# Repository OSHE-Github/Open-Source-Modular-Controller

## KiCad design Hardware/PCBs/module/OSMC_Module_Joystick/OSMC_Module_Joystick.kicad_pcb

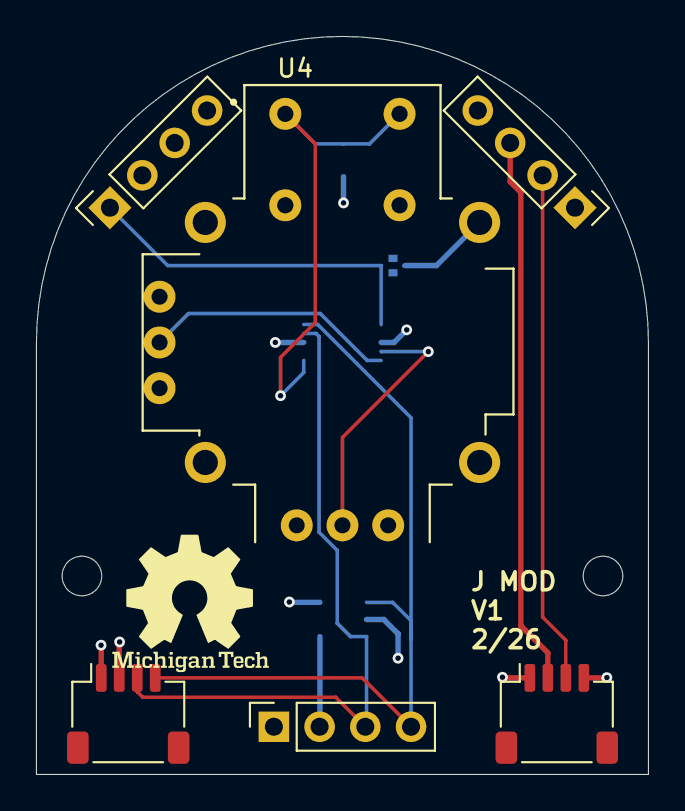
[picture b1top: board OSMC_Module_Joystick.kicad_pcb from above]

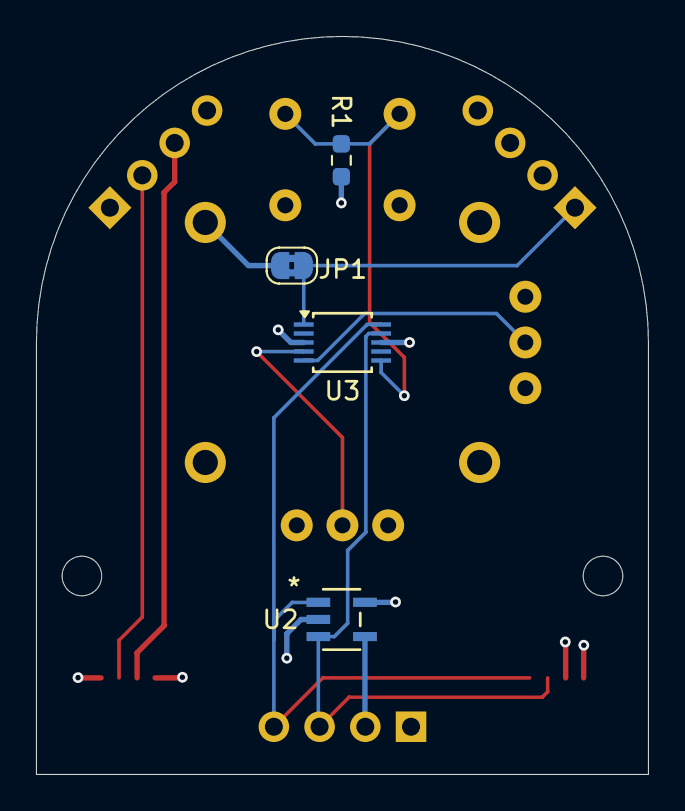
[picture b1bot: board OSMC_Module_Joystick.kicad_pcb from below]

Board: 4 copper layers, 34.0 x 41.0 mm, 6 parts (4 on the bottom side), 10 nets.

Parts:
JP1: SolderJumper_2_Bridged; SolderJumper-2_P1.3mm_Bridged2Bar_RoundedPad1.0x1.5mm
R1: 100K; R_0603_1608Metric_Pad0.98x0.95mm_HandSolder
U1: OSMC Module Board w/pins; Module standard pin large
U2: 24LC02BT-I/OT; SOT-23-5_MC_MCH
U3: ADS1115IDGS; TSSOP-10_3x3mm_P0.5mm
U4: COM-09032; XDCR_COM-09032

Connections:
/3v3: R1.2, U1.2 (Vdd), U1.6 (Vdd), U1.12 (Det), U1.13 (Int), U2.4 (VCC), U3.8 (VDD), U4.H1 (H+), U4.V1 (V+)
/5V: U1.10 (5V), U1.15 (5V)
/A1: JP1.2 (B), U1.20 (A1), U3.1 (ADDR)
/INT: U1.11 (OPT), U1.14 (OPT)
/SCL: U1.4 (SCL), U1.8 (SCL), U2.1 (SCL), U3.10 (SCL)
/SDA: U1.3 (SDA), U1.7 (SDA), U2.3 (SDA), U3.9 (SDA)
GND: JP1.1 (A), U1.1 (Gnd), U1.5 (Gnd), U1.9 (Gnd), U1.16 (GND), U2.2 (VSS), U2.5 (WP), U3.3 (GND), U4.B2A (SEL-), U4.B2B (SEL-), U4.H3 (H-), U4.S1 (SHIELD), U4.S2 (SHIELD__1), U4.S3 (SHIELD__2), U4.S4 (SHIELD__3), U4.V3 (V-)
unnamed: U3.4 (AIN0), U4.H2 (H)
unnamed: U3.5 (AIN1), U4.V2 (V)
unnamed: R1.1, U3.6 (AIN2), U4.B1A (SEL+), U4.B1B (SEL+)

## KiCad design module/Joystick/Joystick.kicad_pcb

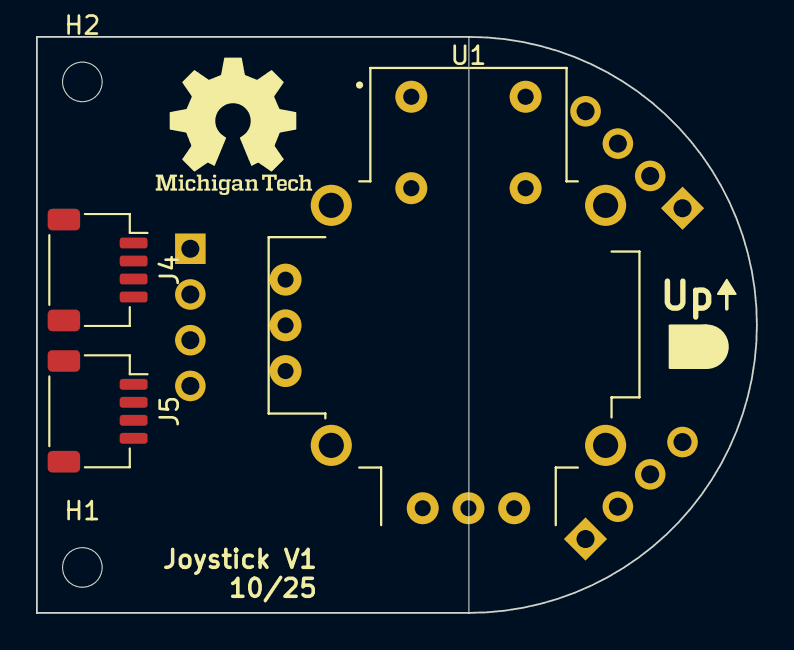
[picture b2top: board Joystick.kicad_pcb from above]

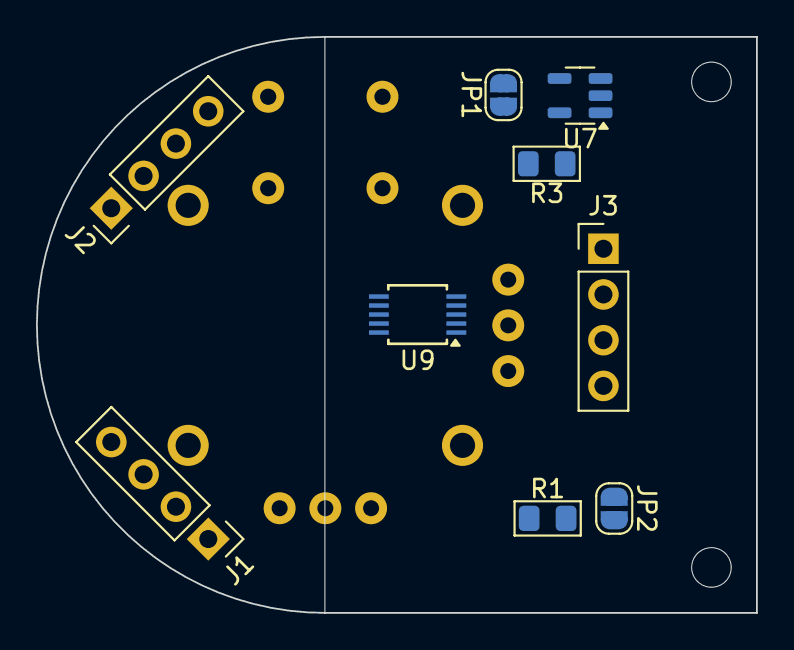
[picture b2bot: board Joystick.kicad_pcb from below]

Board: 2 copper layers, 40.0 x 32.0 mm, 14 parts (9 on the bottom side), 10 nets, no tracks yet.

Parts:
H1, H2: MountingHole; MountingHole_2.2mm_M2
J1: Right Arm; PinHeader_1x04_P2.54mm_Vertical
J2: Right Leg; PinHeader_1x04_P2.54mm_Vertical
J3: Header 1; PinHeader_1x04_P2.54mm_Vertical
J4: Left Arm; JST_SH_SM04B-SRSS-TB_1x04-1MP_P1.00mm_Horizontal
J5: Header 1; JST_SH_SM04B-SRSS-TB_1x04-1MP_P1.00mm_Horizontal
JP1: WP; SolderJumper-2_P1.3mm_Open_RoundedPad1.0x1.5mm
JP2: int; SolderJumper-2_P1.3mm_Open_RoundedPad1.0x1.5mm
R1, R3: 100k; R_0805_2012Metric_Pad1.15x1.40mm_HandSolder
U1: COM-09032; XDCR_COM-09032
U7: 24AA02-OT; SOT-23-5
U9: ADS1115IDGS; TSSOP-10_3x3mm_P0.5mm

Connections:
+5V: U1.H1 (H+), U1.V1 (V+)
/5V: J1.1, J5.1
/Gnd: J1.2, J3.4, J4.4, J5.2, R1.1, R3.1, U7.2 (V_{SS}), U9.1 (ADDR), U9.3 (GND)
/IO1: J2.4, J5.3
/SCL: J3.1, J4.1, U7.1 (SCL), U9.10 (SCL)
/SDA: J3.2, J4.2, U7.3 (SDA), U9.9 (SDA)
/Vdd: J3.3, J4.3, JP1.2 (B), JP2.2 (B), U7.4 (V_{CC}), U9.8 (VDD)
/int: J1.4, J5.4, JP2.1 (A), R1.2
/wp: JP1.1 (A), R3.2, U7.5 (WP)
GND: U1.B2A (SEL-), U1.H3 (H-), U1.S1 (SHIELD), U1.S2 (SHIELD__1), U1.S3 (SHIELD__2), U1.S4 (SHIELD__3), U1.V3 (V-)

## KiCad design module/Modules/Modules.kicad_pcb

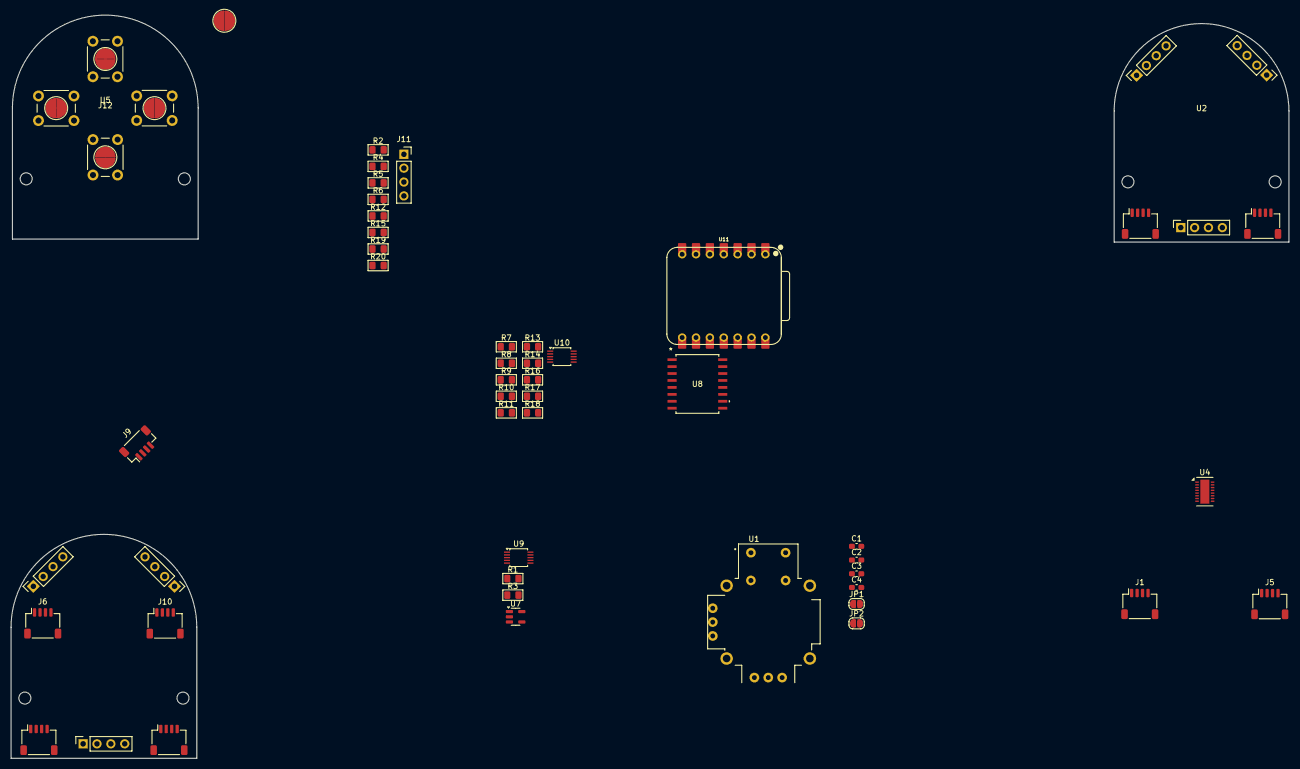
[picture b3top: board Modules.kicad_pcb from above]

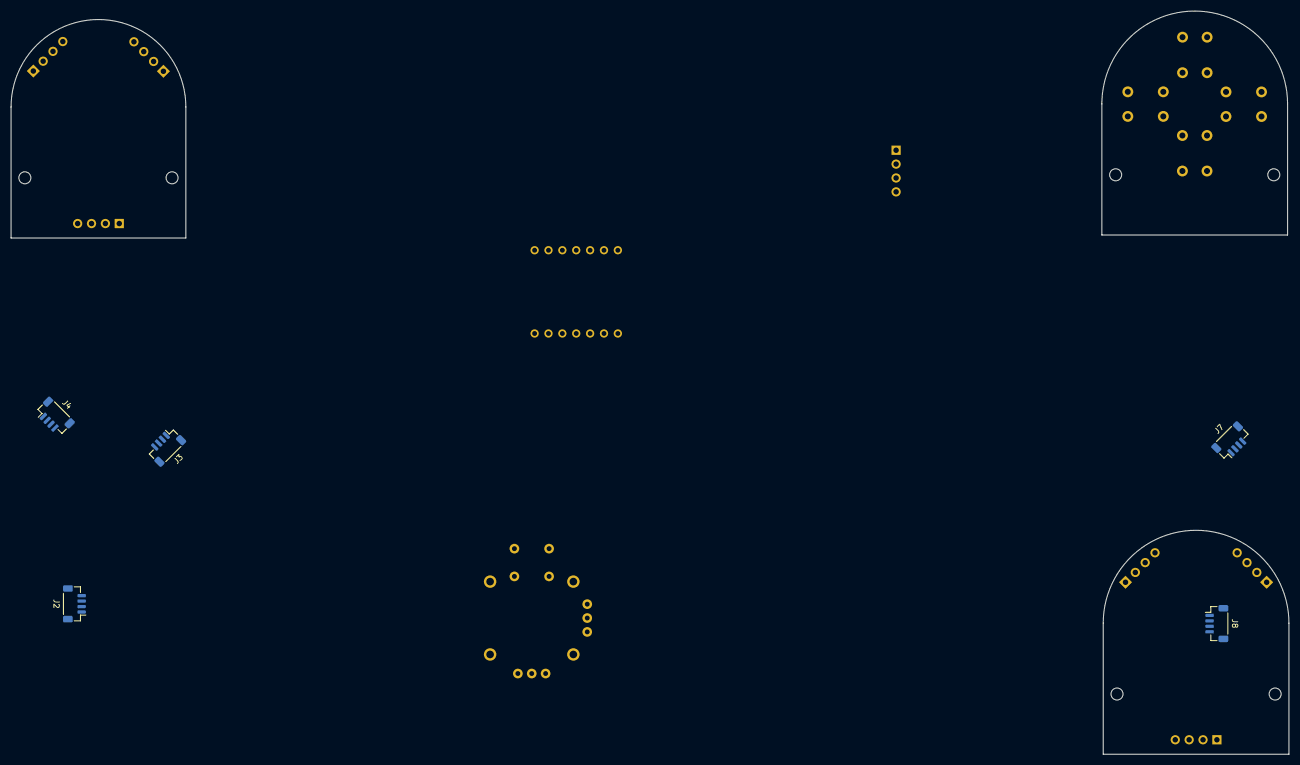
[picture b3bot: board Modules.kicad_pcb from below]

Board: 2 copper layers, 49 parts (5 on the bottom side), 32 nets, no tracks yet.

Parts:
C1, C2: .1 u; C_0603_1608Metric_Pad1.08x0.95mm_HandSolder
C3, C4: C; C_0603_1608Metric_Pad1.08x0.95mm_HandSolder
J1, J5, J6, J10: JST SH; JST_SH_SM04B-SRSS-TB_1x04-1MP_P1.00mm_Horizontal
J2, J3, J4, J7, J8, J9: Conn_01x04; JST_SH_BM04B-SRSS-TB_1x04-1MP_P1.00mm_Vertical
J11: JST SH; PinSocket_1x04_P2.54mm_Vertical
J12: Conn_01x08_Socket; Button Spacing
JP1: WP; SolderJumper-2_P1.3mm_Open_RoundedPad1.0x1.5mm
JP2: Det; SolderJumper-2_P1.3mm_Open_RoundedPad1.0x1.5mm
R1, R2, R3, R4, R5, R6: 100k; R_0805_2012Metric_Pad1.15x1.40mm_HandSolder
R7, R8, R9, R10, R11, R12, R13, R14, R15, R16, R17, R18, R19, R20: 10k; R_0805_2012Metric_Pad1.15x1.40mm_HandSolder
SW1: SW_Push; Membrane Button semi 4 mm
U1: COM-09032; XDCR_COM-09032
U2: OSMC Module Board w/pins; Module standard pin small
U4: OSMC Module Board; DFN-16-1EP_3x5mm_P0.5mm_EP1.66x4.4mm
U5: OSMC Module Board w/pins; Module standard large
U6: OSMC Module Board; Module standard pin large
U7: 24AA02-OT; SOT-23-5
U8: PCF8574DWR; DW16-L
U9: ADS1115IDGS; TSSOP-10_3x3mm_P0.5mm
U10: LTC4317; TSSOP-10_3x3mm_P0.5mm
U11: XIAO-ESP32-S3-DIP

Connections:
/5V: C3.1, C4.1, J4.2, J5.2, J9.2, J10.2, U11.14 (5V)
/B0: R2.2, U8.4 (P0)
/B1: R4.2, U8.5 (P1)
/B2: R5.2, U8.6 (P2)
/B3: R6.2, U8.7 (P3)
/Det: J4.4, J9.4, JP2.1 (A), R1.2
/Gnd: C1.2, C2.2, C3.2, C4.2, J1.1, J2.4, J3.2, J3.3, J3.4, J4.1, J5.1, J6.1, J7.2, J7.3, J7.4, J8.4, J9.1, J10.1, J11.1, R1.1, R3.1, U1.B2A (SEL-), U1.H3 (H-), U1.S1 (SHIELD), U1.S2 (SHIELD__1), U1.S3 (SHIELD__2), U1.S4 (SHIELD__3), U1.V3 (V-), U7.2 (V_{SS}), U8.1 (A0), U8.2 (A1), U8.3 (A2), U8.8 (GND), U9.1 (ADDR), U9.3 (GND), U11.13 (GND)
/Opt: J4.3, J9.3
/SCL: J1.4, J2.1, J6.4, J8.1, J11.4, R12.2, U7.1 (SCL), U8.14 (SCL), U9.10 (SCL), U11.6 (PA9_A5_D5_SCL)
/SCL0: R7.2, R8.2
/SCL1: R9.2, R10.2, R20.2, U11.9 (PA7_A8_D8_SCK)
/SDA: J1.3, J2.2, J6.3, J8.2, J11.3, R15.2, U7.3 (SDA), U8.15 (SDA), U9.9 (SDA), U11.5 (PA8_A4_D4_SDA)
/SDA1: R19.2, U11.10 (PA5_A9_D9_MISO)
/Vdd: C1.1, C2.1, J1.2, J2.3, J6.2, J8.3, J11.2, JP1.2 (B), JP2.2 (B), R2.1, R4.1, R5.1, R6.1, R12.1, R15.1, R19.1, R20.1, U1.H1 (H+), U1.V1 (V+), U7.4 (V_{CC}), U8.16 (VDD), U9.8 (VDD), U11.12 (3V3)
/X1: U1.H2 (H), U9.5 (AIN1)
/Y1: U1.V2 (V), U9.4 (AIN0)
/Z1: U1.B1A (SEL+), U9.7 (AIN3)
/int: J5.4, J10.4, U8.13 (~INT), U9.2 (ALERT/RDY)
/wp: JP1.1 (A), R3.2, U7.5 (WP)
GND: R13.2, R16.2, U10.1 (GND), U10.3 (XORH2), U10.4 (XORL2)
unnamed: U2.10 (5V), U2.15 (5V)
unnamed: U2.12 (Det), U2.13 (Det)
unnamed: U2.1 (Gnd), U2.5 (Gnd), U2.9 (Gnd), U2.16 (GND)
unnamed: U2.11 (OPT), U2.14 (OPT)
unnamed: U2.4 (SCL), U2.8 (SCL)
unnamed: U2.3 (SDA), U2.7 (SDA)
unnamed: U2.2 (Vdd), U2.6 (Vdd)
unnamed: R18.2, U10.8 (ENABLE1)
unnamed: R17.2, U10.2 (ENABLE2)
unnamed: R11.2, R13.1, U10.5 (XORH1)
unnamed: R14.2, R16.1, U10.6 (XORL1)
VDD: R7.1, R8.1, R9.1, R10.1, R11.1, R14.1, R17.1, R18.1, U10.7 (VCC)

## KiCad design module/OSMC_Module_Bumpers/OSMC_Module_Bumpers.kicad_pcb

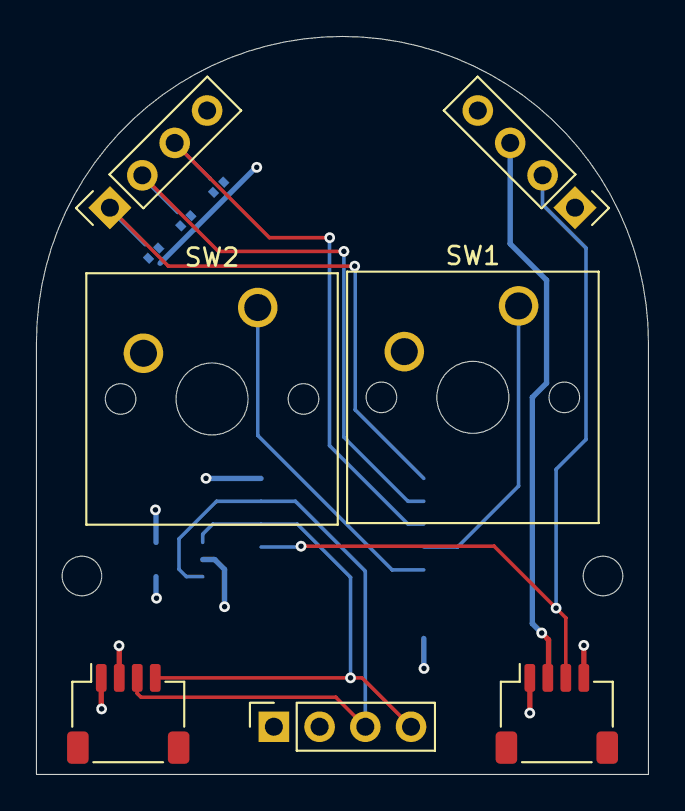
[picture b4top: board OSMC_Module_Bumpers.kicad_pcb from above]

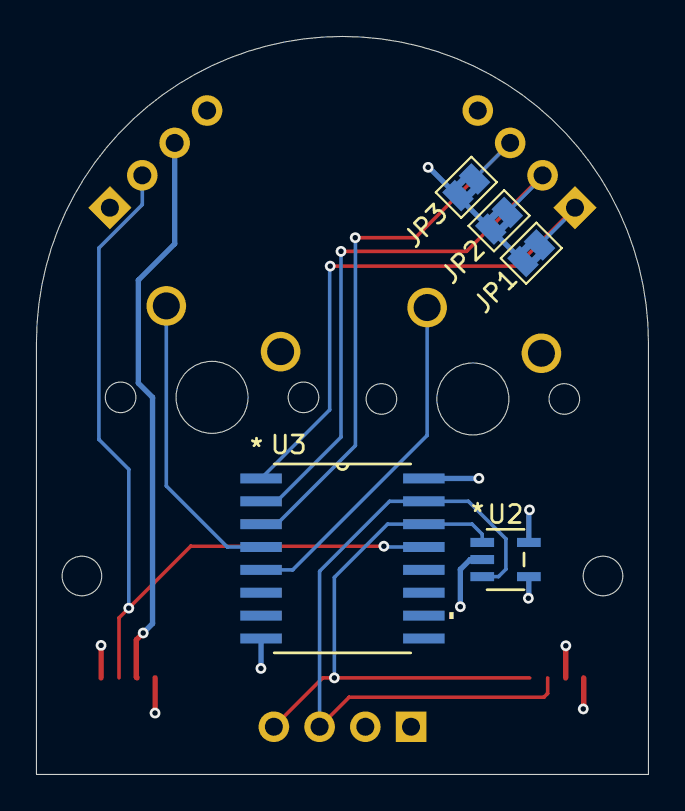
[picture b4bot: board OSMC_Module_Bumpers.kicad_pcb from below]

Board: 4 copper layers, 34.0 x 41.0 mm, 8 parts (5 on the bottom side), 11 nets.

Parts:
JP1, JP2, JP3: SolderJumper_2_Bridged; SolderJumper-2_P1.3mm_Bridged2Bar_Pad1.0x1.5mm
SW1, SW2: SW_SPST; SW_Cherry_MX_1.00u_PCB
U1: OSMC Module Board w/pins; Module standard pin large
U2: 24LC02BT-I/OT; SOT-23-5_MC_MCH
U3: PCF8574DWR; DW16

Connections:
/3v3: U1.2 (Vdd), U1.6 (Vdd), U1.12 (Det), U1.13 (Int), U2.4 (VCC), U3.16 (VCC)
/5V: U1.10 (5V), U1.15 (5V)
/A0: JP1.1 (A), U1.20 (A1), U3.1 (A0)
/A1: JP2.1 (A), U1.19 (A2), U3.2 (A1)
/A2: JP3.1 (A), U1.18 (A3), U3.3 (A2)
/B1: SW1.1 (A), U3.4 (P0)
/B2: SW2.1 (A), U3.5 (P1)
/INT: U1.11 (OPT), U1.14 (OPT), U3.13 (*INT)
/SCL: U1.4 (SCL), U1.8 (SCL), U2.1 (SCL), U3.14 (SCL)
/SDA: U1.3 (SDA), U1.7 (SDA), U2.3 (SDA), U3.15 (SDA)
GND: JP1.2 (B), JP2.2 (B), JP3.2 (B), SW1.2 (B), SW2.2 (B), U1.1 (Gnd), U1.5 (Gnd), U1.9 (Gnd), U1.16 (GND), U2.2 (VSS), U2.5 (WP), U3.8 (GND)

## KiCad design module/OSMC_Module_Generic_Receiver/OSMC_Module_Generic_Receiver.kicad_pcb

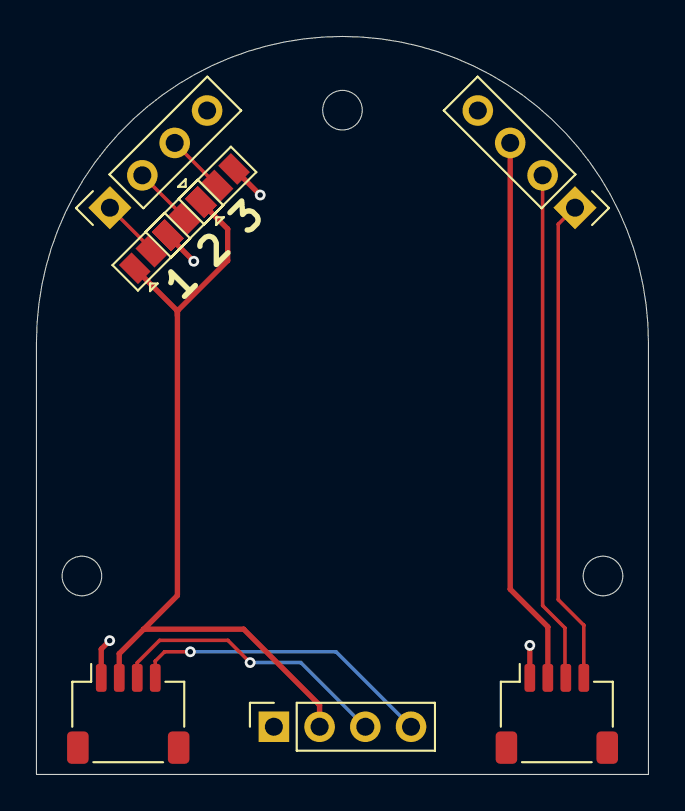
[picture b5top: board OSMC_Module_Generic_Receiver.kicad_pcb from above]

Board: 2 copper layers, 34.0 x 41.0 mm, 4 parts (0 on the bottom side), 10 nets.

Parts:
JP9, JP10, JP11: SolderJumper_3_Open; SolderJumper-3_P1.3mm_Open_Pad1.0x1.5mm
U1: OSMC Module Board w/pins; Module standard pin large

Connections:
/3v3: JP9.1 (A), JP10.1 (A), JP11.1 (A), U1.2 (Vdd), U1.6 (Vdd)
/5V: U1.10 (5V), U1.15 (5V)
/Det: U1.12 (Det), U1.13 (Int)
/INT: U1.11 (OPT), U1.14 (OPT)
/SCL: U1.4 (SCL), U1.8 (SCL)
/SDA: U1.3 (SDA), U1.7 (SDA)
GND: JP9.3 (B), JP10.3 (B), JP11.3 (B), U1.1 (Gnd), U1.5 (Gnd), U1.9 (Gnd), U1.16 (GND)
unnamed: JP9.2 (C), U1.18 (A3)
unnamed: JP10.2 (C), U1.19 (A2)
unnamed: JP11.2 (C), U1.20 (A1)

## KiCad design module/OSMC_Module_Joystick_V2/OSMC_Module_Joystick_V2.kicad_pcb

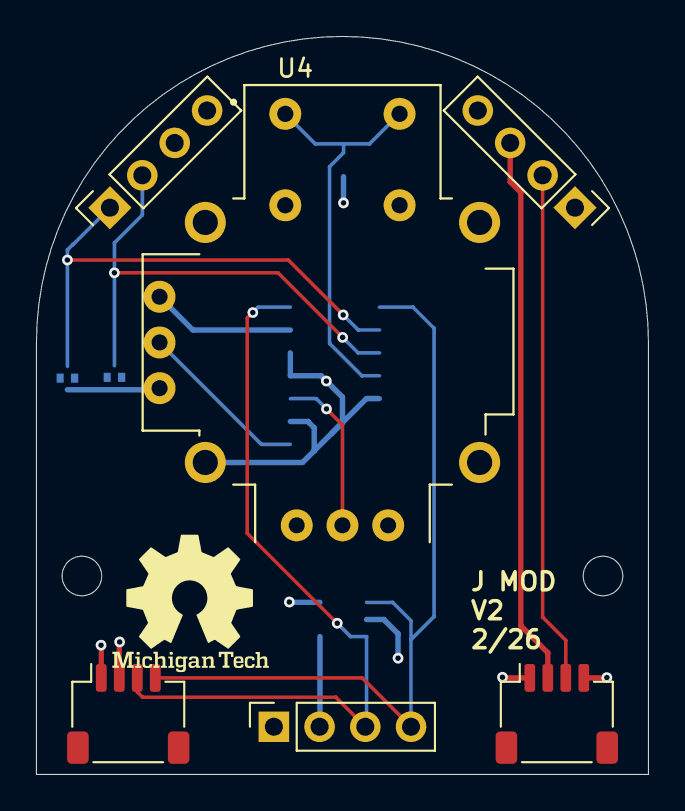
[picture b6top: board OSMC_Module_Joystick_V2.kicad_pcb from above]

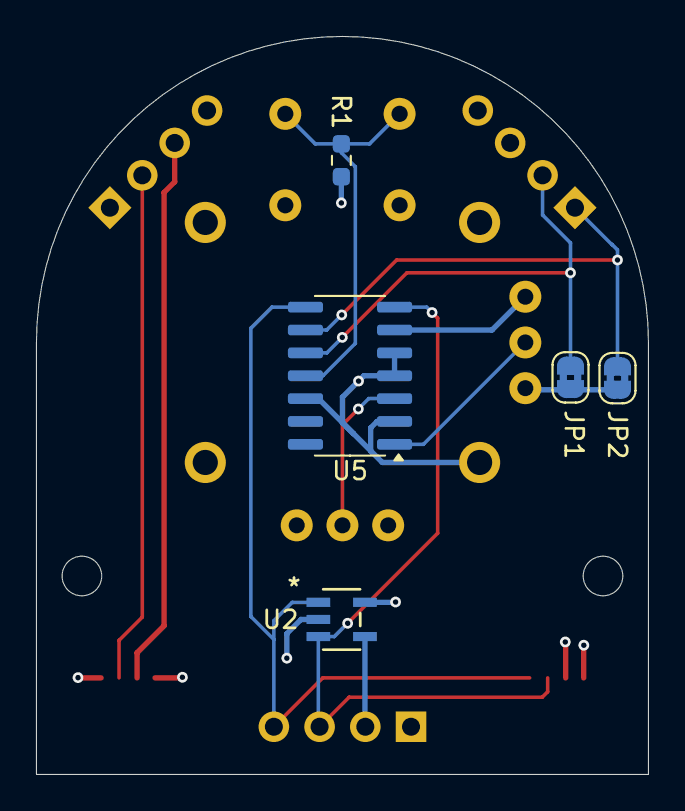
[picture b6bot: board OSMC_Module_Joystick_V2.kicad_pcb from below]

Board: 4 copper layers, 34.0 x 41.0 mm, 7 parts (5 on the bottom side), 11 nets.

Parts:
JP1, JP2: SolderJumper_2_Bridged; SolderJumper-2_P1.3mm_Bridged2Bar_RoundedPad1.0x1.5mm
R1: 100K; R_0603_1608Metric_Pad0.98x0.95mm_HandSolder
U1: OSMC Module Board w/pins; Module standard pin large
U2: 24LC02BT-I/OT; SOT-23-5_MC_MCH
U4: COM-09032; XDCR_COM-09032
U5: MCP3428x-xSL; SOIC-14_3.9x8.7mm_P1.27mm

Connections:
/3v3: R1.2, U1.2 (Vdd), U1.6 (Vdd), U1.12 (Det), U1.13 (Int), U2.4 (VCC), U4.H1 (H+), U4.V1 (V+), U5.6 (V_{DD})
/5V: U1.10 (5V), U1.15 (5V)
/A0: JP2.2 (B), U1.20 (A1), U5.9 (Adr0)
/A1: JP1.2 (B), U1.19 (A2), U5.10 (Adr1)
/INT: U1.11 (OPT), U1.14 (OPT)
/SCL: U1.4 (SCL), U1.8 (SCL), U2.1 (SCL), U5.8 (SCL)
/SDA: U1.3 (SDA), U1.7 (SDA), U2.3 (SDA), U5.7 (SDA)
GND: JP1.1 (A), JP2.1 (A), U1.1 (Gnd), U1.5 (Gnd), U1.9 (Gnd), U1.16 (GND), U2.2 (VSS), U2.5 (WP), U4.B2A (SEL-), U4.B2B (SEL-), U4.H3 (H-), U4.S1 (SHIELD), U4.S2 (SHIELD__1), U4.S3 (SHIELD__2), U4.S4 (SHIELD__3), U4.V3 (V-), U5.2 (CH1-), U5.4 (CH2-), U5.5 (V_{SS}), U5.12 (CH3-)
unnamed: U4.H2 (H), U5.3 (CH2+)
unnamed: U4.V2 (V), U5.1 (CH1+)
unnamed: R1.1, U4.B1A (SEL+), U4.B1B (SEL+), U5.11 (CH3+)

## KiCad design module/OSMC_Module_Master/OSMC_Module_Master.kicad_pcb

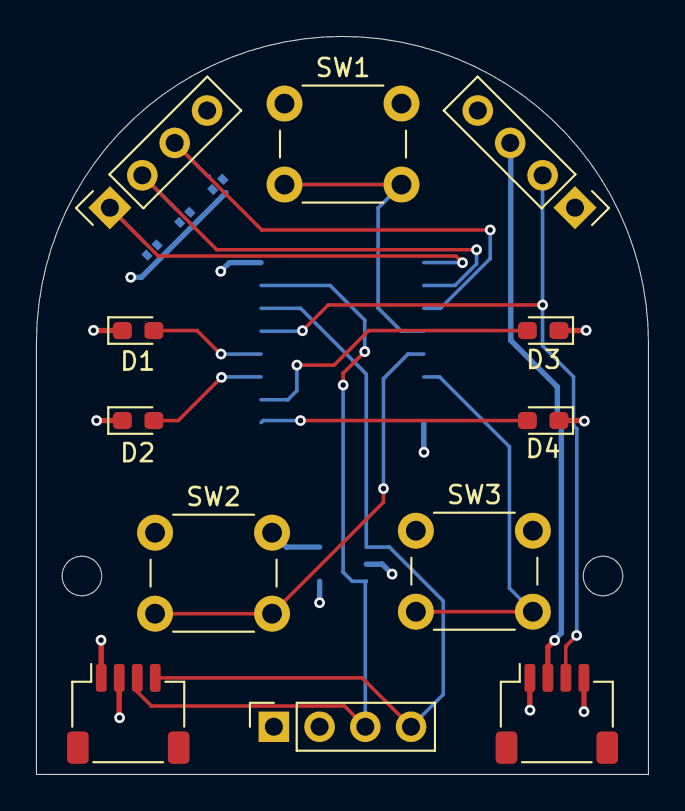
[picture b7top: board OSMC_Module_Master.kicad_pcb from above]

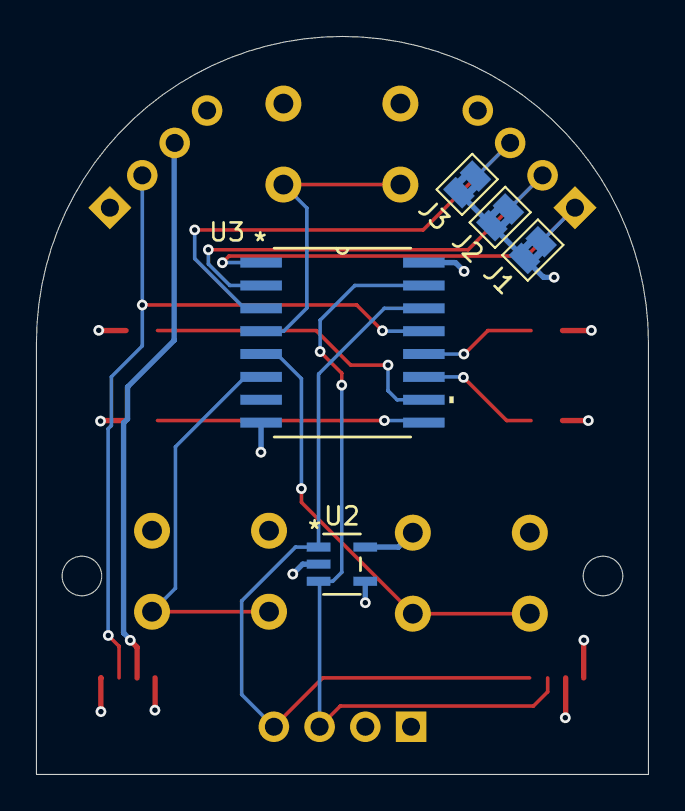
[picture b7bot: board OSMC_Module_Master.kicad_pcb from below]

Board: 4 copper layers, 34.0 x 41.0 mm, 13 parts (5 on the bottom side), 16 nets.

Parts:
D1, D2, D3, D4: LED; LED_0603_1608Metric_Pad1.05x0.95mm_HandSolder
J1, J2, J3: SolderJumper_2_Bridged; SolderJumper-2_P1.3mm_Bridged2Bar_Pad1.0x1.5mm
SW1, SW2, SW3: SW_Push; SW_PUSH_6mm
U1: OSMC Module Board w/pins; Module standard pin large
U2: 24LC02BT-I/OT; SOT-23-5_MC_MCH
U3: PCF8574DWR; DW16

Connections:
/3v3: D1.1 (K), D2.1 (K), D3.1 (K), D4.1 (K), U1.2 (Vdd), U1.6 (Vdd), U1.12 (Det), U1.13 (Int), U2.4 (VCC), U3.16 (VCC)
/5V: U1.10 (5V), U1.15 (5V)
/A0: J1.1 (A), U1.20 (A1), U3.1 (A0)
/A1: J2.1 (A), U1.19 (A2), U3.2 (A1)
/A2: J3.1 (A), U1.18 (A3), U3.3 (A2)
/B1: SW1.2, U3.4 (P0)
/B2: SW2.2, U3.5 (P1)
/B3: SW3.2, U3.6 (P2)
/D1: D1.2 (A), U3.12 (P7)
/D2: D2.2 (A), U3.11 (P6)
/D3: D3.2 (A), U3.10 (P5)
/D4: D4.2 (A), U3.9 (P4)
/INT: U1.11 (OPT), U1.14 (OPT), U3.13 (*INT)
/SCL: U1.4 (SCL), U1.8 (SCL), U2.1 (SCL), U3.14 (SCL)
/SDA: U1.3 (SDA), U1.7 (SDA), U2.3 (SDA), U3.15 (SDA)
GND: J1.2 (B), J2.2 (B), J3.2 (B), SW1.1, SW2.1, SW3.1, U1.1 (Gnd), U1.5 (Gnd), U1.9 (Gnd), U1.16 (GND), U2.2 (VSS), U2.5 (WP), U3.8 (GND)

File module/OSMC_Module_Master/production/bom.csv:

Designator,Footprint,Quantity,Value,LCSC Part #
"D1, D2, D3, D4",0603,4,LED,
"SW1, SW2, SW3",SW_PUSH_6mm,3,SW_Push,
U1,Module standard pin large,1,OSMC Module Board w/pins,
U2,SOT-23-5_MC_MCH,1,24LC02BT-I/OT,
U3,DW16,1,PCF8574DWR,
